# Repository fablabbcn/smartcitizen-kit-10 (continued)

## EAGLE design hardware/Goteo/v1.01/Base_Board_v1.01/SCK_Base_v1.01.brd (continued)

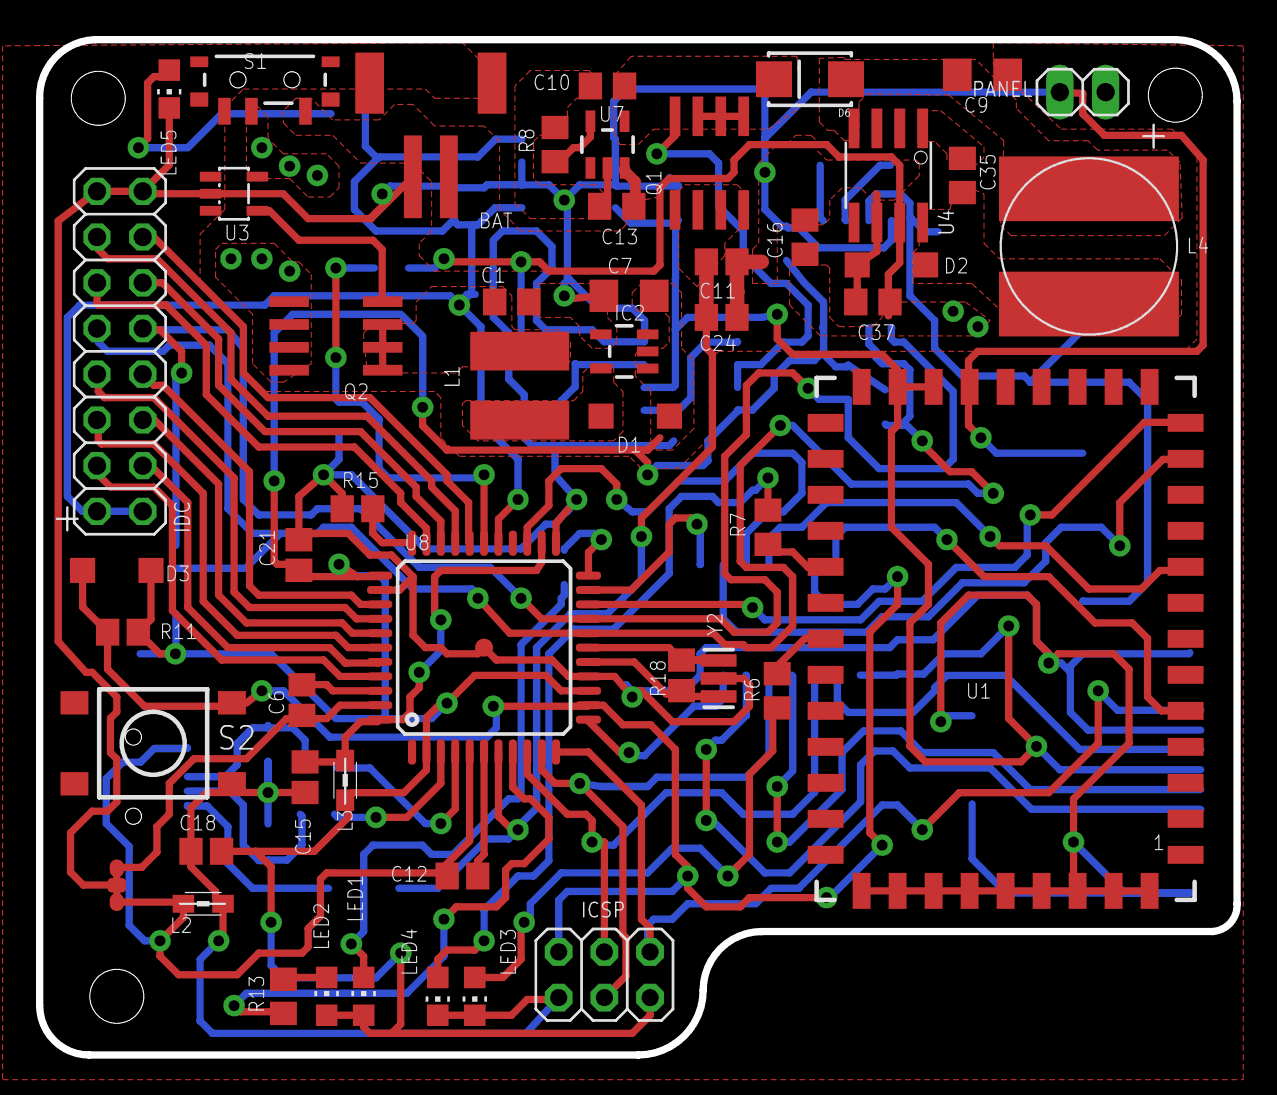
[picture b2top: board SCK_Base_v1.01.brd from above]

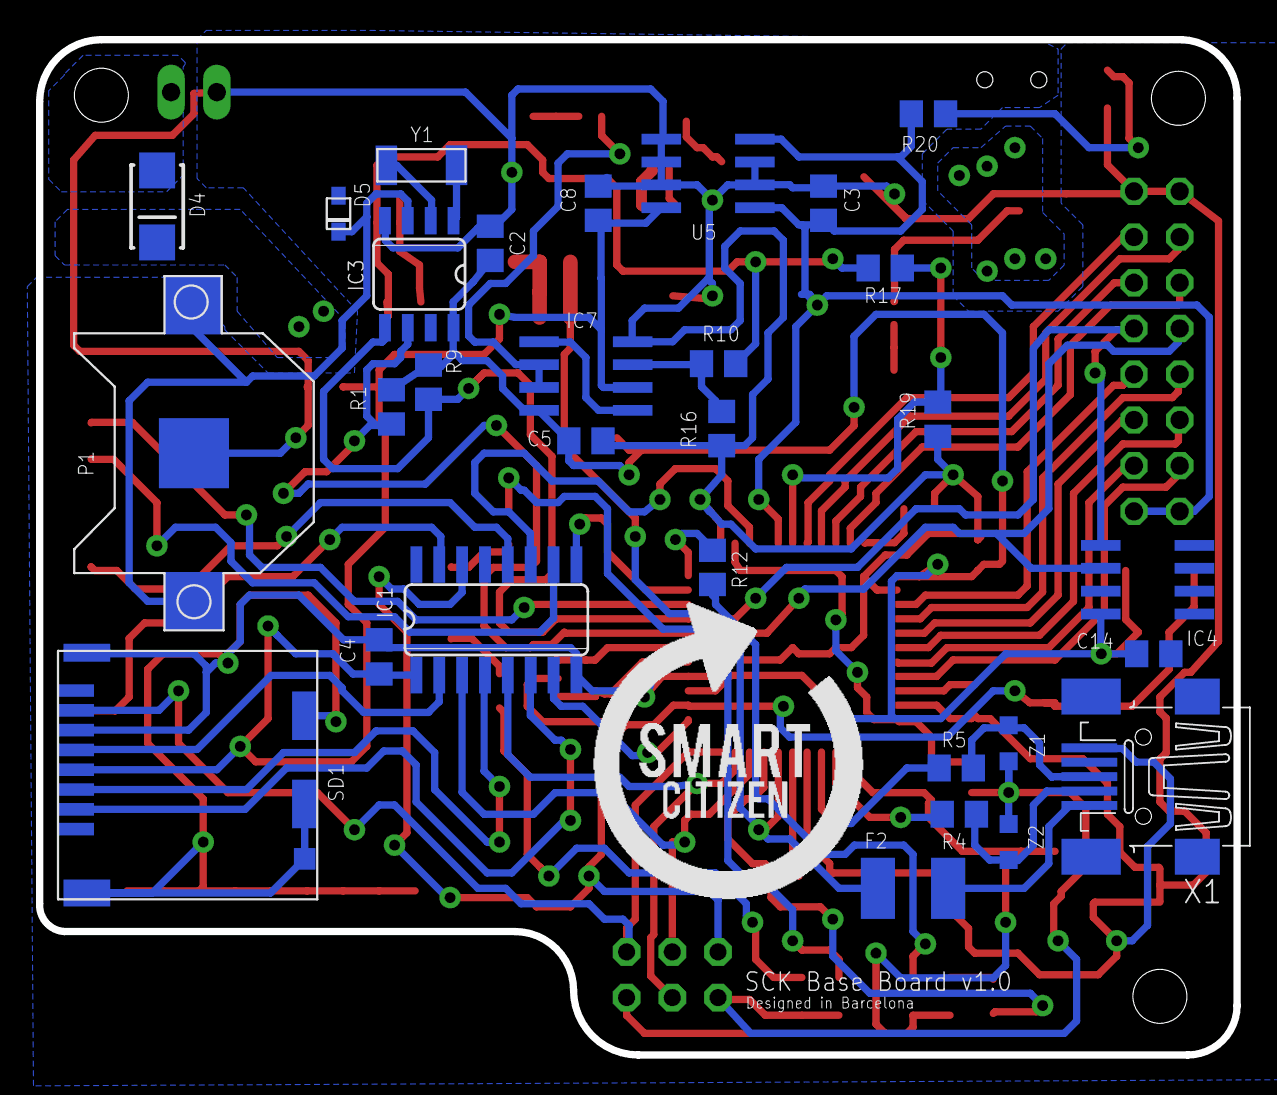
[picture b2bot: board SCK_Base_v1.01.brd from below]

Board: 2 copper layers, 66.5 x 56.4 mm, 81 parts (30 on the bottom side), 71 nets.

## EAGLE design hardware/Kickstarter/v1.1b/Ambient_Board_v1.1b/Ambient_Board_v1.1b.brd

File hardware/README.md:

Smart Citizen Kit
=================

###Smart Citizen Kit Ambient Sensor Board versions

| Smart Citizen Kit |           | SCK 1.0 (Goteo Board)       | SCK 1.1 (Kickstarter Board)       |
|:-----------|:---------:|:---------------------------:|:---------------------------:|
| **Data Board**        |           |                                                                                  |                                                                                     |
| **MCU**               |           | ATMEGA32U4                                                                       | ATMEGA32U4                                                                          |
| **Clock**             |           | 16Mhz                                                                            | 8Mhz                                                                                |
| **WiFi**             |           | Microchip RN-131 802.11 b/g                                                                            | Microchip RN-131 802.11 b/g                                                                                |
| **Firmware**         |           | https://github.com/fablabbcn/Smart-Citizen-Kit                                   | https://github.com/fablabbcn/Smart-Citizen-Kit                                      |
| **Design files**      |           | https://github.com/fablabbcn/Smart-Citizen-Kit/tree/master/hardware/Goteo/v1.01  | https://github.com/fablabbcn/Smart-Citizen-Kit/tree/master/hardware/Kickstarter     |
| **Ambient Board**     |           |                                                                                  |                                                                                     |
| **Light**             | *Part*      | PVD-P8001                                                                        | BH1730FVC                                                                           |
|                   | *Type*      | LDR Analog Light Sensor                                                          | Digital Ambient Light Sensor                                                        |
|                   | *Units*     | %                                                                                | Lux                                                                                 |
|                   | *Datasheet* | https://github.com/fablabbcn/Smart-Citizen-Kit/wiki/Datasheets/PDV-P8001.pdf     | https://github.com/fablabbcn/Smart-Citizen-Kit/wiki/Datasheets/BH-1730FCV.pdf       |
|                   | Firmware  | `SCKAmbient::getLight();`                                                           | `SCKAmbient::getLight():`                                                              |
| **Temp**              | *Part*      | DHT22                                                                            | HPP828E031 (SHT21)                                                                  |
|                   | *Type*      | Digital Temperature and Relative Humidity Sensor                                 | Digital Temperature and Relative Humidity Sensor                                    |
|                   | *Units*     | ºC                                                                               | ºC                                                                                  |
|                   | *Datasheet* | https://github.com/fablabbcn/Smart-Citizen-Kit/wiki/Datasheets/DHT22.pdf         | https://github.com/fablabbcn/Smart-Citizen-Kit/wiki/Datasheets/HTU-21D.pdf          |
|                   | Firmware  | `SCKAmbient::getDHT22();` `SCKAmbient::getHumidity();`                               | `SCKAmbient::getSHT21();` `SCKAmbient::getTemperature();`                               |
| **Humidity**          | *Part*      | DHT22                                                                            | HPP828E031 (SHT21)                                                                  |
|                   | *Type*      | Digital Temperature and Relative Humidity Sensor                                 | Digital Temperature and Relative Humidity Sensor                                    |
|                   | *Units*     | % Rel                                                                            | % Rel                                                                               |
|                   | *Datasheet* | https://github.com/fablabbcn/Smart-Citizen-Kit/wiki/Datasheets/DHT22.pdf         | https://github.com/fablabbcn/Smart-Citizen-Kit/wiki/Datasheets/HTU-21D.pdf          |
|                   | Firmware  | `SCKAmbient::getDHT22();` `SCKAmbient::getHumidity();`                               | `SCKAmbient::getSHT21();` `SCKAmbient::getHumidity();`                                  |
| **Noise**             | *Part*      | POM-3044P-R                                                                      | POM-3044P-R                                                                         |
|                   | *Type*      | Electret microphone with envelop follower sound pressure sensor                  | Electret microphone with envelop follower sound pressure sensor                     |
|                   | *Units*     | dB                                                                               | dB                                                                                  |
|                   | *Datasheet* | https://github.com/fablabbcn/Smart-Citizen-Kit/wiki/Datasheets/POM-3044P-R.pdf   | https://github.com/fablabbcn/Smart-Citizen-Kit/wiki/Datasheets/POM-3044P-R.pdf      |
|                   | *Firmware*  | `SCKAmbient::getNoise();`                                                          | `SCKAmbient::getNoise();`                                                             |
| **CO**                | *Part*      | MICS-5525                                                                        | MiCS-4514                                                                           |
|                   | *Type*      | MOS CO gas sensor                                                                | MOS CO and NO2 gas sensor                                                           |
|                   | *Units*     | kOhm (ppm)                                                                       | kOhm (ppm)                                                                          |
|                   | *Datasheet* | https://github.com/fablabbcn/Smart-Citizen-Kit/wiki/Datasheets/MICS-5525_CO.pdf  | https://github.com/fablabbcn/Smart-Citizen-Kit/wiki/Datasheets/MiCS-4514_CO_NO2.pdf |
|                   | *Firmware*  | `SCKAmbient::getMICS();`                                                           | `SCKAmbient::getMICS();`                                                              |
| **NO2**               | *Part*      | MICS-2710                                                                        | MiCS-4514                                                                           |
|                   | *Type*      | MOS NO2 gas sensor                                                               | MOS CO and NO2 gas sensor                                                           |
|                   | *Units*     | kOhm (ppm)                                                                       | kOhm (ppm)                                                                          |
|                   | *Datasheet* | https://github.com/fablabbcn/Smart-Citizen-Kit/wiki/Datasheets/MICS-2710_NO2.pdf | https://github.com/fablabbcn/Smart-Citizen-Kit/wiki/Datasheets/MiCS-4514_CO_NO2.pdf |
|                   | *Firmware*  | `SCKAmbient::getMICS();`                                                           | `SCKAmbient::getMICS();`                                                              |

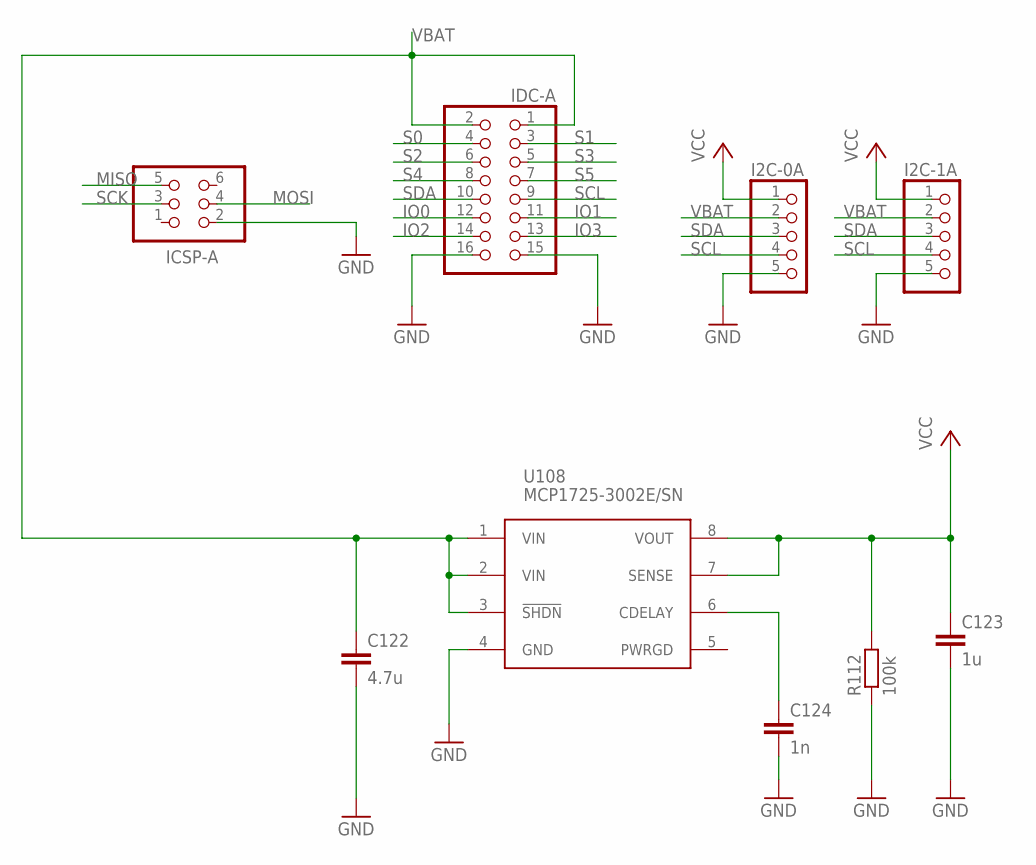
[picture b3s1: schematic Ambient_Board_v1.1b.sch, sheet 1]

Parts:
C122: 4.7u; C0805
C123: 1u; C0805
C124: 1n; C0603K
I2C-0A, I2C-1A: PINHD-1X5; 1X05
ICSP-A: ICSP-A; 2X03
IDC-A: PINHD-2X8; 2X08
R112: 100k; R0603
U108: MCP1725-3002E/SN; SOIC8

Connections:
GND: C122.2, C123.2, C124.2, I2C-0A.5, I2C-1A.5, ICSP-A.2, IDC-A.15, IDC-A.16, R112.1, U108.4 (GND); also elsewhere on the board
IO0: IDC-A.12; also elsewhere on the board
IO1: IDC-A.11; also elsewhere on the board
IO2: IDC-A.14; also elsewhere on the board
IO3: IDC-A.13; also elsewhere on the board
MISO: ICSP-A.5
MOSI: ICSP-A.4
unnamed: C124.1, U108.6 (CDELAY)
S0: IDC-A.4; also elsewhere on the board
S1: IDC-A.3; also elsewhere on the board
S2: IDC-A.6; also elsewhere on the board
S3: IDC-A.5; also elsewhere on the board
S4: IDC-A.8; also elsewhere on the board
S5: IDC-A.7
SCK: ICSP-A.3
SCL: I2C-0A.4, I2C-1A.4, IDC-A.9; also elsewhere on the board
SDA: I2C-0A.3, I2C-1A.3, IDC-A.10; also elsewhere on the board
VBAT: C122.1, I2C-0A.2, I2C-1A.2, IDC-A.1, IDC-A.2, U108.1 (VIN), U108.2 (VIN), U108.3 (!SHDN); also elsewhere on the board
VCC: C123.1, I2C-0A.1, I2C-1A.1, R112.2, U108.7 (SENSE), U108.8 (VOUT); also elsewhere on the board

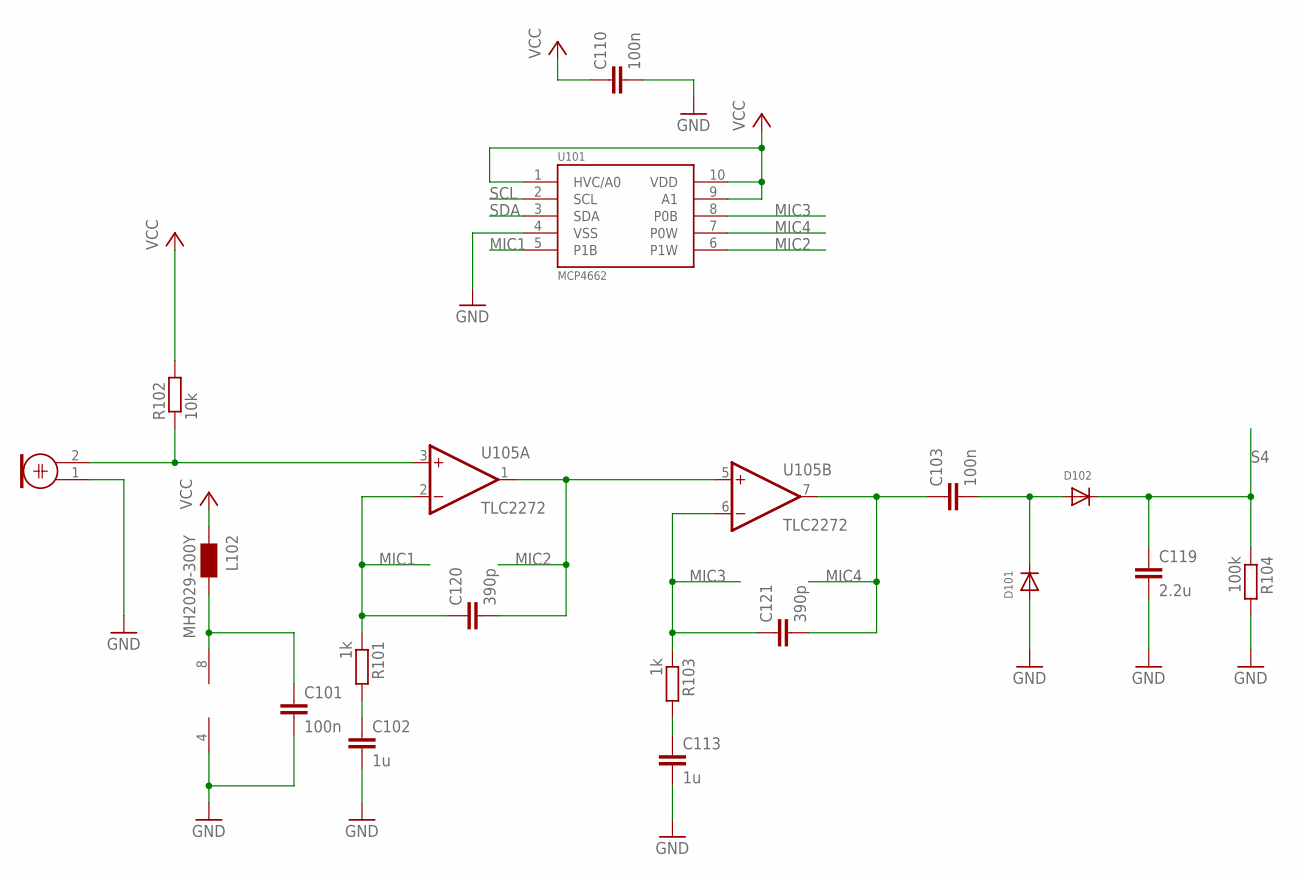
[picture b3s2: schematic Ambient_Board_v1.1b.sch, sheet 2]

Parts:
C101, C103, C110: 100n; C0603
C102, C113: 1u; C0805
C119: 2.2u; C0805
C120, C121: 390p; C0603
D101, D102: DIODESOD-323F; SOD-323F
L102: MH2029-300Y; 0805
M101: POM-3044P-R; WM-63PR
R101, R103: 1k; R0603
R102: 10k; R0603
R104: 100k; R0603
U101: MCP4662; MSOP10
U105: TLC2272; SO08

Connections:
GND: C101.2, C102.2, C110.2, C113.2, C119.2, D101.A, M101.1, R104.2, U101.4 (VSS), U105.4 (V-); also elsewhere on the board
MIC1: C120.1, R101.1, U101.5 (P1B), U105.2 (-IN)
MIC2: C120.2, U101.6 (P1W), U105.1 (OUT), U105.5 (+IN)
MIC3: C121.1, R103.1, U101.8 (P0B), U105.6 (-IN)
MIC4: C103.1, C121.2, U101.7 (P0W), U105.7 (OUT)
unnamed: M101.2, R102.1, U105.3 (+IN)
unnamed: C102.1, R101.2
unnamed: C103.2, D101.C, D102.A
unnamed: C101.1, L102.2, U105.8 (V+)
unnamed: C113.1, R103.2
S4: C119.1, D102.C, R104.1; also elsewhere on the board
SCL: U101.2 (SCL); also elsewhere on the board
SDA: U101.3 (SDA); also elsewhere on the board
VCC: C110.1, L102.1, R102.2, U101.1 (HVC/A0), U101.9 (A1), U101.10 (VDD); also elsewhere on the board

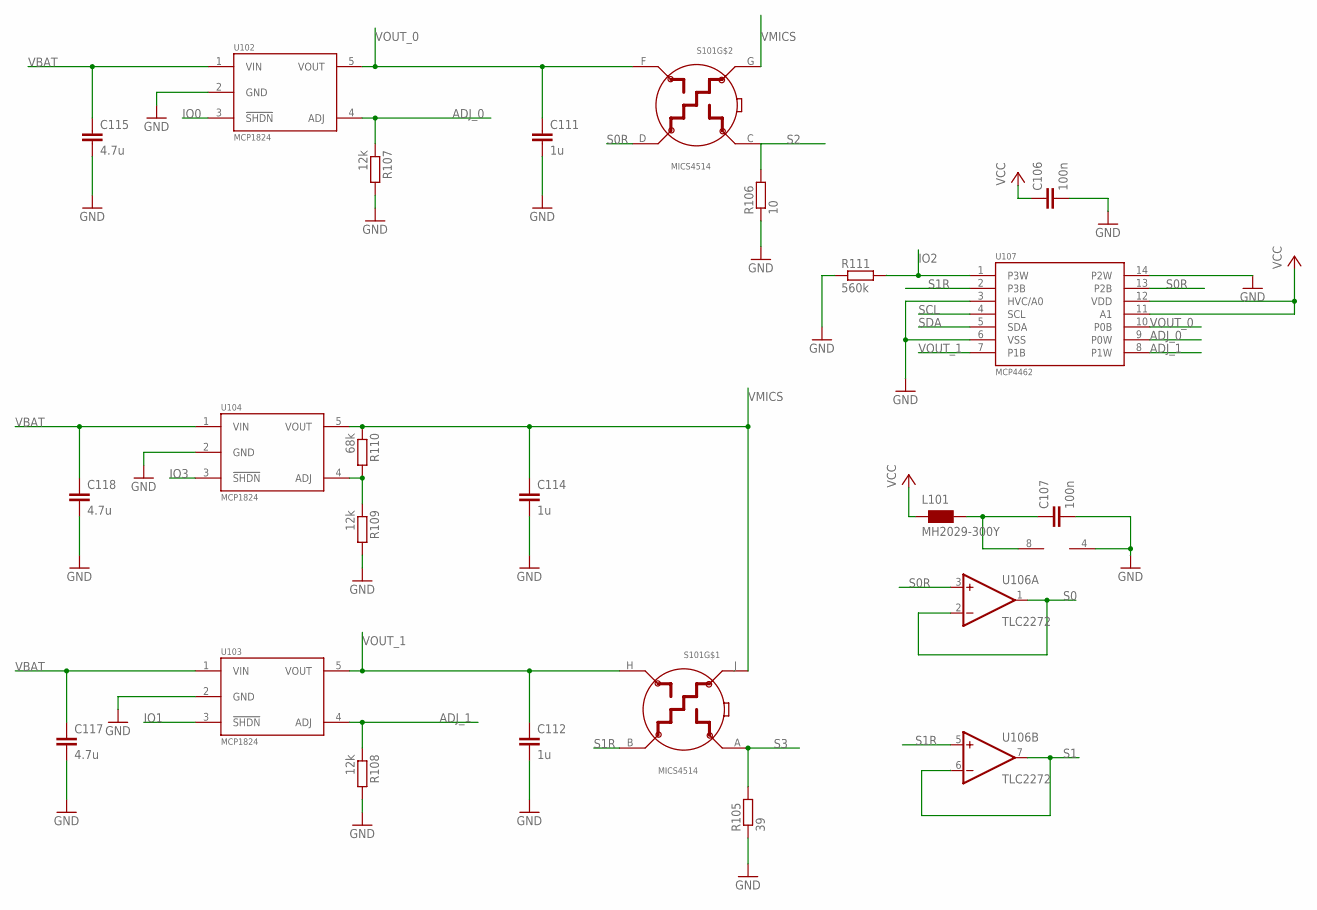
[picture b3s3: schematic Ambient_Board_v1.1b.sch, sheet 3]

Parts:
C106, C107: 100n; C0603
C111, C112, C114: 1u; C0805
C115, C117, C118: 4.7u; C0805
L101: MH2029-300Y; 0805
R105: 39; R0603
R106: 10; R0603
R107, R108, R109: 12k; R0603
R110: 68k; R0603
R111: 560k; R0603
S101: MICS4514; MICS_SMD
U102, U103, U104: MCP1824; SOT23-5L
U106: TLC2272; SO08
U107: MCP4462; TSSOP14

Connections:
ADJ_0: R107.1, U102.4 (ADJ), U107.9 (P0W)
ADJ_1: R108.1, U103.4 (ADJ), U107.8 (P1W)
GND: C106.2, C107.2, C111.2, C112.2, C114.2, C115.2, C117.2, C118.2, R105.1, R106.1, R107.2, R108.2, R109.2, R111.1, U102.2 (GND), U103.2 (GND), U104.2 (GND), U106.4 (V-), U107.3 (HVC/A0), U107.6 (VSS), U107.14 (P2W); also elsewhere on the board
IO0: U102.3 (!SHDN); also elsewhere on the board
IO1: U103.3 (!SHDN); also elsewhere on the board
IO2: R111.2, U107.1 (P3W); also elsewhere on the board
IO3: U104.3 (!SHDN); also elsewhere on the board
unnamed: C107.1, L101.2, U106.8 (V+)
unnamed: R109.1, R110.2, U104.4 (ADJ)
S0: U106.1 (OUT), U106.2 (-IN); also elsewhere on the board
S0R: S101.D (4), U106.3 (+IN), U107.13 (P2B)
S1: U106.6 (-IN), U106.7 (OUT); also elsewhere on the board
S1R: S101.B (4), U106.5 (+IN), U107.2 (P3B)
S2: R106.2, S101.C (1); also elsewhere on the board
S3: R105.2, S101.A (1); also elsewhere on the board
SCL: U107.4 (SCL); also elsewhere on the board
SDA: U107.5 (SDA); also elsewhere on the board
VBAT: C115.1, C117.1, C118.1, U102.1 (VIN), U103.1 (VIN), U104.1 (VIN); also elsewhere on the board
VCC: C106.1, L101.1, U107.11 (A1), U107.12 (VDD); also elsewhere on the board
VMICS: C114.1, R110.1, S101.G (2), S101.J (2), U104.5 (VOUT)
VOUT_0: C111.1, S101.F (3), U102.5 (VOUT), U107.10 (P0B)
VOUT_1: C112.1, S101.H (3), U103.5 (VOUT), U107.7 (P1B)

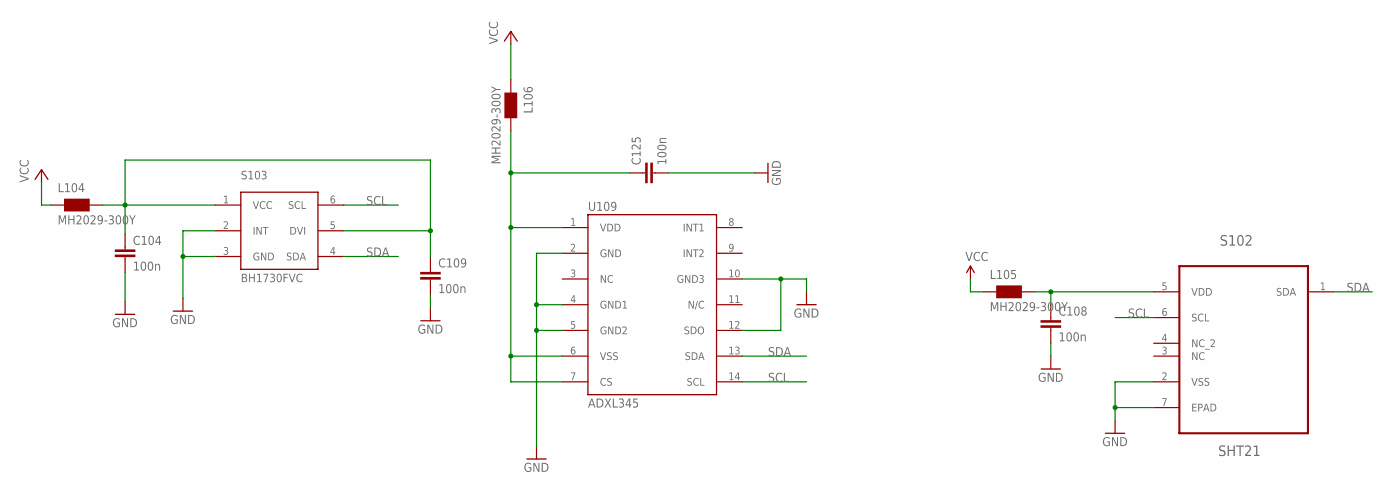
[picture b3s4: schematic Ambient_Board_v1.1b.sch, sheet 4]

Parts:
C104, C108, C109, C125: 100n; C0603
L104, L105, L106: MH2029-300Y; 0805
S102: SHT21; DFN300X300X110-7N
S103: BH1730FVC; WSOF6
U109: ADXL345; LGA14

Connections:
GND: C104.2, C108.2, C109.2, C125.2, S102.2 (VSS), S102.7 (EPAD), S103.2 (INT), S103.3 (GND), U109.2 (GND), U109.4 (GND1), U109.5 (GND2), U109.10 (GND3), U109.12 (SDO); also elsewhere on the board
unnamed: C125.1, L106.2, U109.1 (VDD), U109.6 (VSS), U109.7 (CS)
unnamed: C108.1, L105.2, S102.5 (VDD)
unnamed: C104.1, C109.1, L104.2, S103.1 (VCC), S103.5 (DVI)
SCL: S102.6 (SCL), S103.6 (SCL), U109.14 (SCL); also elsewhere on the board
SDA: S102.1 (SDA), S103.4 (SDA), U109.13 (SDA); also elsewhere on the board
VCC: L104.1, L105.1, L106.1; also elsewhere on the board

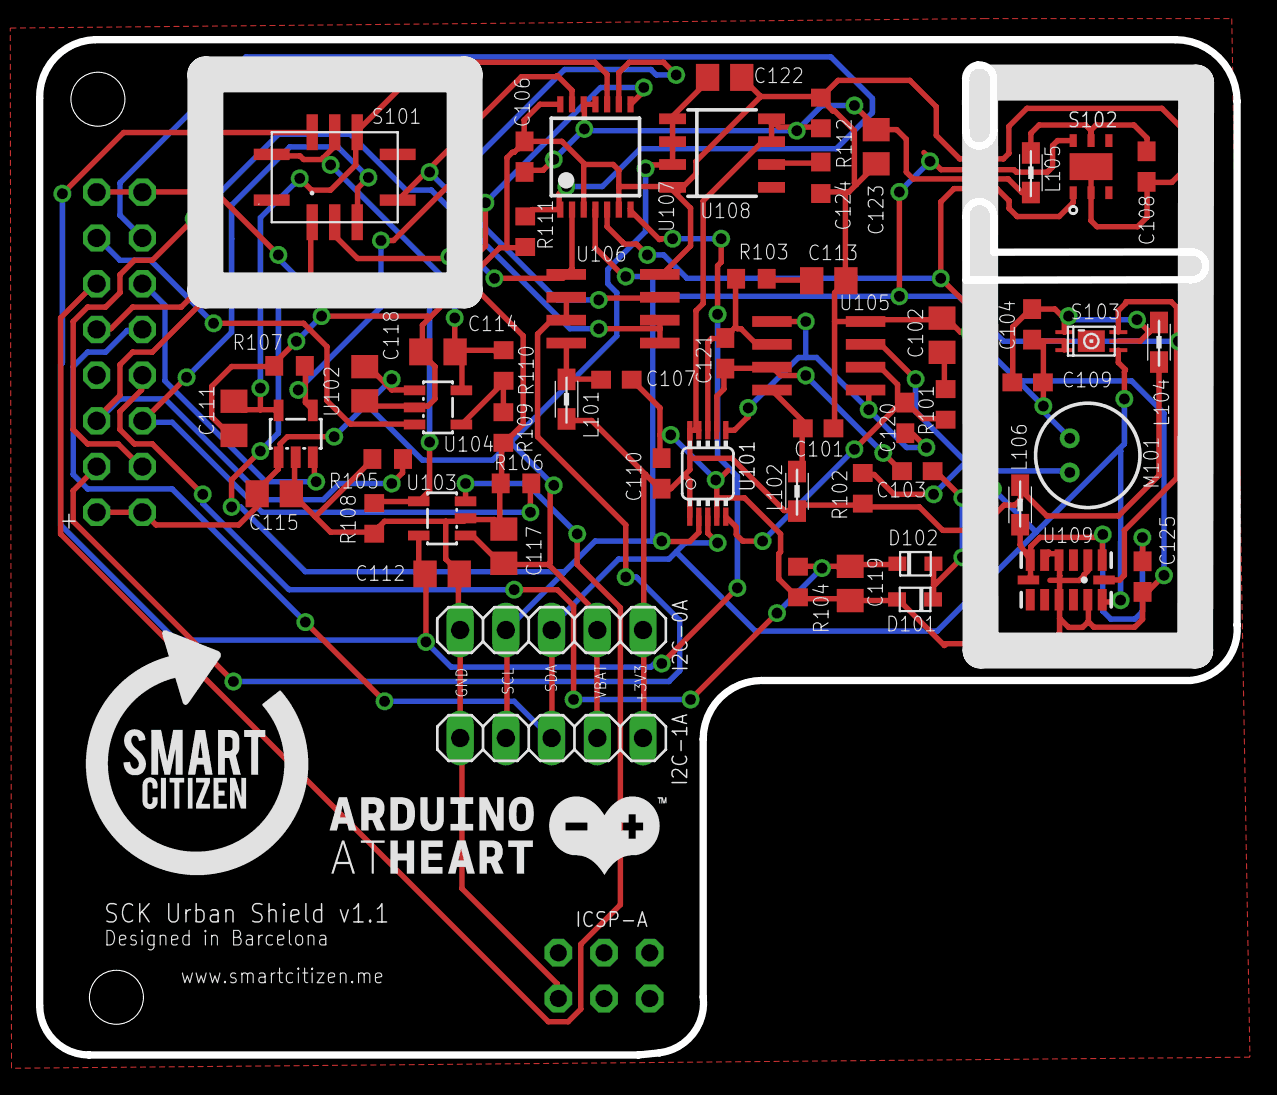
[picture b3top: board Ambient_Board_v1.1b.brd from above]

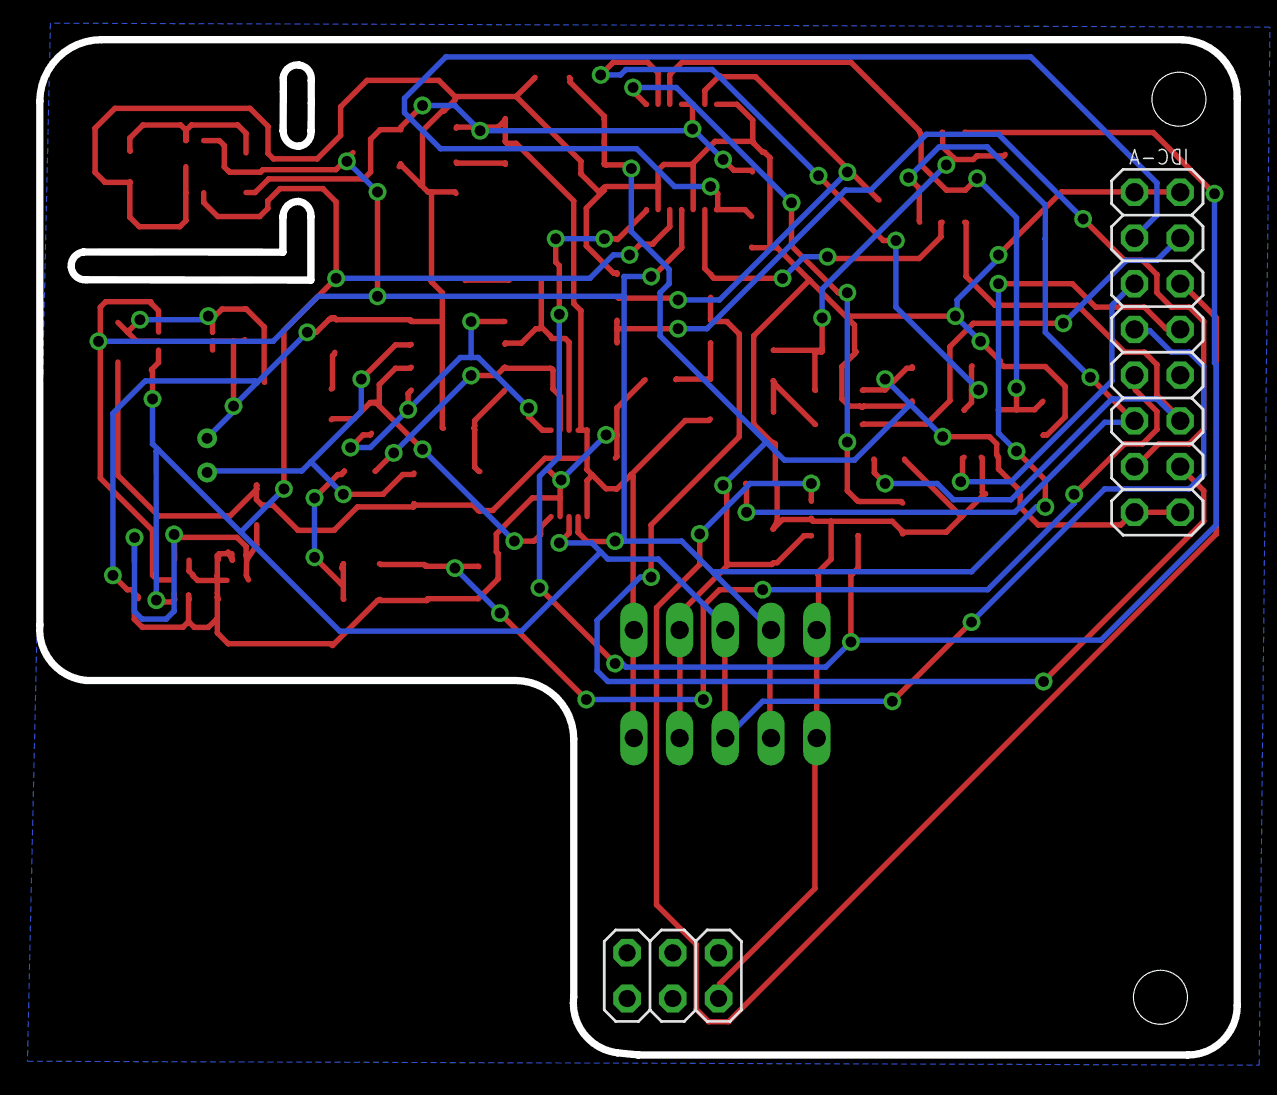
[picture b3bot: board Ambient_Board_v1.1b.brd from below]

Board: 2 copper layers, 66.5 x 56.4 mm, 59 parts (2 on the bottom side), 36 nets.

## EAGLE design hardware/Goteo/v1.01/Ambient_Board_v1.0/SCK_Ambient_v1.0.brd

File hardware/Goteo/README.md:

Smart-Citizen-Kit
=================

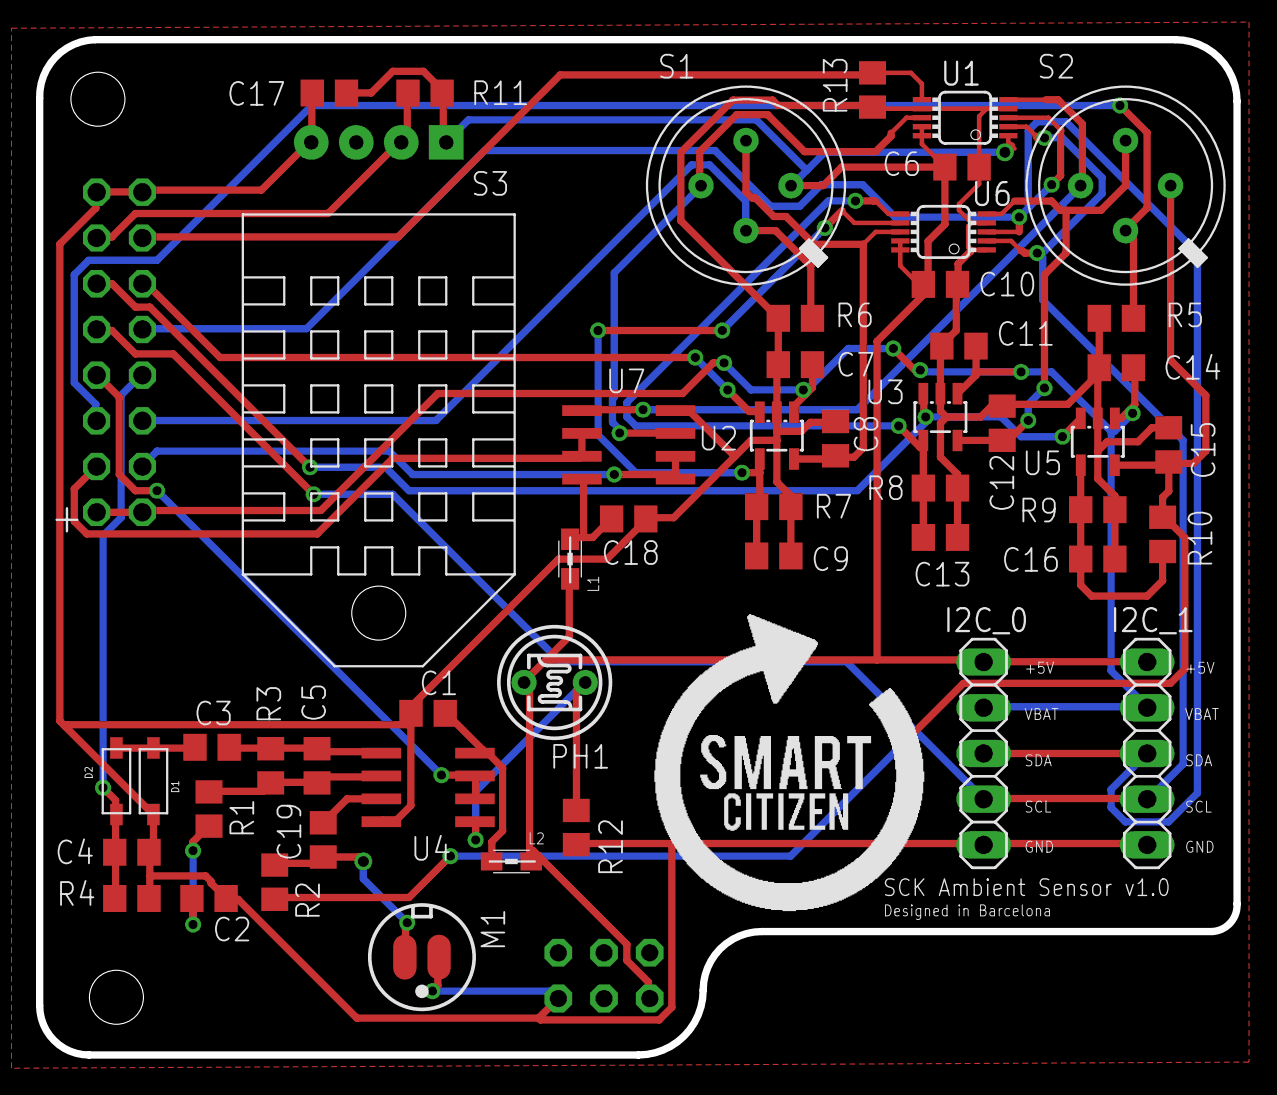
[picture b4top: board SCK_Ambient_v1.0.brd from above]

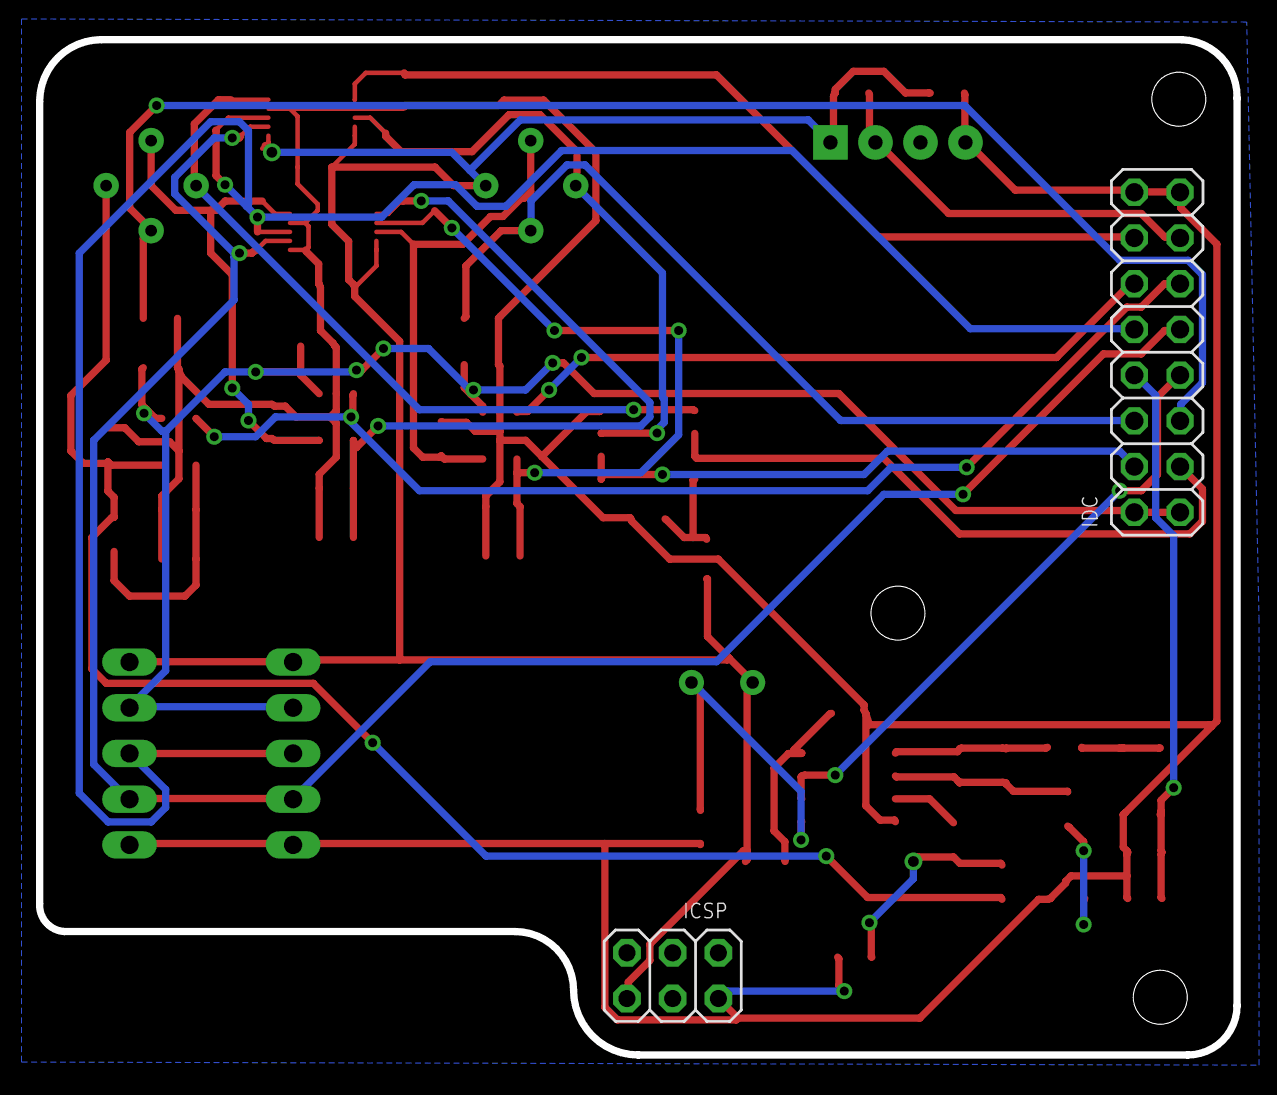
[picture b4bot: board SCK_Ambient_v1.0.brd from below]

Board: 2 copper layers, 66.5 x 56.4 mm, 52 parts (2 on the bottom side), 32 nets.

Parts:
C1, C3, C6, C10, C17, C18: 100n; C0805
C2, C4, C19: 2.2u; C0805
C5: 10p; C0805
C7, C8, C11, C12, C14, C15: 10u; C0805
C9, C13, C16: 100p; C0805
D1, D2: SOD-123
I2C_0, I2C_1: 1X05
ICSP: ICSP; 2X03
IDC: 2X08
L1, L2: MH2029-300Y; 0805
M1: ELECTRET_MICROPHON-WM-61A; WM-61A
PH1: A1050_09; T0-46-A10XX
R1: 4K7; R0805
R2: 10K; R0805
R3, R13: 560k; R0805
R4: 100K; R0805
R5, R6: 10; R0805
R7, R8: 82k; R0805
R9: 180K; R0805
R10: 200K; R0805
R11: 1K; R0805
R12: 2K2; R0805
S1: MICS-5525; E2V
S2: MICS-2710; E2V
S3: RHT22
U1, U6: MCP4662; MSOP10
U2, U3, U5: TC1071; SOT23-5L
U4, U7: TL082D; SO08

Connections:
+5V: C6.1, C10.1, C17.1, I2C_0.1, I2C_1.1, ICSP.6, L1.1, L2.1, PH1.1, R11.1, S1.2, S3.1, U1.1, U1.9, U1.10, U6.9, U6.10
ADJ_0: C9.1, R7.1, U2.4, U6.7
ADJ_1: C13.1, R8.1, U3.4, U6.6
ADJ_2: C16.1, R9.1, R10.2, U5.4
GND: C1.2, C2.2, C4.2, C6.2, C7.2, C8.2, C9.2, C10.2, C11.2, C12.2, C13.2, C14.2, C15.2, C16.2, C17.2, C18.2, D1.A, I2C_0.5, I2C_1.5, ICSP.2, IDC.15, IDC.16, M1.1, R4.2, R5.1, R6.1, R7.2, R8.2, R9.2, R12.2, R13.1, S3.4, U1.4, U1.7, U2.2, U3.2, U4.4, U5.2, U6.1, U6.4, U7.4
IO0: IDC.12, U2.3
IO1: IDC.11, U3.3, U5.3
IO2: IDC.14, R13.2, U1.6
IO3: IDC.13, R11.2, S3.2
unnamed: C19.1, M1.2, R2.1
unnamed: C2.1, R1.2
unnamed: C3.2, D1.C, D2.A
unnamed: C5.1, R1.1, R3.2, U4.2
unnamed: C3.1, C5.2, R3.1, U4.1
unnamed: C1.1, L2.2, U4.8
unnamed: C18.1, L1.2, U7.8
unnamed: PH1.2, R12.1, U4.5
unnamed: C19.2, U4.3
S0: IDC.4, U7.1, U7.2
S0R: S1.4, U1.8, U7.3
S1: IDC.3, U7.6, U7.7
S1R: S2.4, U1.5, U7.5
S2: IDC.6, R6.2, S1.1
S3: IDC.5, R5.2, S2.1
S4: C4.1, D2.C, IDC.8, R4.1
S5: IDC.7, U4.6, U4.7
SCL: I2C_0.4, I2C_1.4, IDC.9, U1.2, U6.2
SDA: I2C_0.3, I2C_1.3, IDC.10, U1.3, U6.3
VBAT1: C7.1, C11.1, C14.1, I2C_0.2, I2C_1.2, IDC.1, IDC.2, U2.1, U3.1, U5.1
VOUT_0: C8.1, S1.3, U2.5, U6.8
VOUT_1: C12.1, S2.3, U3.5, U6.5
VOUT_2: C15.1, R2.2, R10.1, S2.2, U5.5

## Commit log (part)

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2013-02-09 first demo code
2013-02-10 SCK BETA V0.3
    Pushing the Sck_test_beta_v0_3 firmware for the SmartCitizen KIT
2013-02-11 Fixed some bugs in the startup process. Sometimes the wifi module crashes. Necessary to update the firmware to 2.38.3
2013-02-11 Added sketch to control wifly module using Arduino terminal. Recommended update firmware after connecting to wifly network. Command: "ftp upload" + enter
2013-02-11 Revert "no message"
    This reverts commit b9999eb610b8e5de27009ff5f1576d843702d1a4.
2013-02-11 readme file
2013-02-12 Added sketch to control wifly module using Arduino terminal. Recommended update firmware after connecting to wifly network.
2013-02-14 Info to upload firmware and restart wifly module to factory setup
2013-04-24 New version compatible with COSM. Change the SSID and password in configDefault file, then change your feed and APIKEY.
2013-04-24 Sketch for updating WIFly firmware. Put your SSID and password in the main program Sck_ftp_update.ino
2013-04-24 minor changes
2013-04-26 Solved problem with smart citizen kit usb configuration using Smart Citizen platform.
2013-06-01 solved problem when wifi is disconnected for a long time!
2013-07-24 Eagles files of Goteo.org campaign http://www.goteo.org/project/smart-citizen-sensores-ciudadanos
    Smart Citizen Kit BETA version
    - Base Board v1.0
    - Ambient Sensor Board v1.0
2013-07-24 Base Board v1.01 Some improvements:
    - Wifly 3V3 RIN connected to GND
    - Adding new diode for the battery of RTC
2013-08-11 Some problems with eagle original files. Uploaded sources in zip format.
2013-10-01 Nueva version
2013-10-01 Nueva versión
    Se a eliminado gran parte de la libreria SmartCitizen y simplificado
    alguna funciones.
    Añadida compatibilidad a la version 1.1 del SCK Board y Ambient
2013-10-01 Fallo corregido provisionalmente, tiene un desbordamiento de memoria y solo acepta preconfigurar dos redes de memoria.
2013-10-01 Correcciones de cuelgues
2013-10-08 Adquirida compensacion de temperatura by armadillu
2013-10-08 Adquirida mencion al creador de la libreia I2C utilizada
2013-10-19 Correcciones en los sensores de gas
2013-10-19 Correccion de valores negativos de temperatura que provocaba un error al postear
2013-10-20 Adquirida ecuación de conversión a ppm de los sensores de gas
2013-10-27 Cambios introducidos por aposada
2013-10-27 actualizado
2013-10-27 Correcciones en la SD
2013-10-28 Corregido fallo en el primer post del sensor de luz
2013-10-28 Añadido ajuste de reloj de la RTC cada vez que conecta al servidor.
2013-11-04 Actualizada la RTC al chip DS1339
2013-12-09 Limpieza de codigo y se puede seleccionar entre modo RAW y "normal"
2013-12-09 Nueva version del firmware
2013-12-09 Revert "Nueva version del firmware"
    This reverts commit 14413ed2e1d3c47728bc4939659fe5b9d16b2a45.
2013-12-09 Revert "Revert "Nueva version del firmware""
    This reverts commit 48708747a4e2fb564135b2baacb12a41b3a75624.
2013-12-09 Revert "Revert "Revert "Nueva version del firmware"""
    This reverts commit 76695489e06d827ac74d6207b5496909c3cbbf43.
2013-12-09 Correcciones en la RTC
2013-12-11 Activado modo "RAW" y adquirida lista de comandos.
2013-12-11 Añadido nuevo comando
2013-12-13 Correccion medicion de la bateria
2013-12-14 Adquirido nuevo comando para setear el numero de actualizaciones a la vez
2013-12-15 Cambios en las ecuaciones de audio
2013-12-16 Adquirido numero de subversion
2013-12-18 Adquirida version de placa.
2014-01-08 Adquirido modo RAW para los SmartCitizenKit v1.0
2014-01-09 Deshabilitado el modo AP automatico cuando no detecta redes disponibles.
    Ahora solo entra en modo AP cuando se arranca la placa por primera vez.
2014-01-09 Correcciones en modo AP
2014-01-09 Adquirido comando #data para visualizar los datos de la EEPROM
2014-01-09 Adquirido nuevo comando en la lista de comandos
2014-01-10 ajustes del modo AP
2014-01-14 manual cleaning
2014-01-14 clean
2014-01-14 v0.3.0
2014-01-14 v0.6.2
2014-01-14 v0.8.4
2014-01-14 v0.8.5
2014-01-15 updated hardware and readme info
2014-01-16 repo restructure
2014-01-16 links after mig
2014-01-16 Correccion en el checkeo de la EEPROM
2014-01-16 Correccion en la lectura de la EEPROM que puede producir cuelgue del kit
2014-01-16 Importante!! Corrección en la constante VCC, que produce que los valores leeidos en todos los SCK v1.1 sean erroneos!!
2014-01-17 Adquirido provisionalmente el acelerometro ADXL345
2014-01-25 Added full firm and mac commands to sck custom terminal
    Commands added to support the new config under the custom "###"
    terminal mode
2014-02-03 serial bridge WiFly to USB limited CMD Mode
    WiFly Serial Bridge limited to WiFly commands mode to prevent undesired
    debug info when in SCK command mode
2014-02-03 Code Formatting
2014-02-16 Update sck-commands.md
    Fix some spelling an grammar issues.
2014-03-09 Testing wifly acquired
2014-03-09 Wifly_Rescue.ino acquired
2014-03-12 Wifly_Update.ino acquired
2014-03-14 0.8.6 Ready for release
    - Added: WiFly Baudrate autodetect and repair
    - Added: WiFly Auto firmware update
2014-03-18 New utilities and compensation of analog reference voltage
    Utilities:
    Wifly_Update.ino
    Wifly_Rescue.ino
2014-03-18 Now also compiles in Arduino IDE 1.5.6
2014-03-20 SD version adquired
2014-03-21 Improved USB communication, and SD card only version
2014-03-21 Improved USB communication
2014-03-21 Autoupdate correction
2014-03-22 Add ftp server
2014-03-22 Fixed bug in terminal mode
2014-03-23 New version of wifly_terminal
2014-03-23 Connection changes
2014-04-09 New SCK_check
2014-04-10 update sck_check
2014-04-10 update2 sck_check
2014-04-10 update 2 sck_check
2014-04-11 0.8.6 public release
2014-04-15 Translated to English
2014-04-17 release 0.8.6
2014-04-17 release
2014-04-17 release 0.8.6 readme fixes
2014-04-17 Acquired new beta version 0.9
2014-04-17 Keywords deleted
2014-04-18 Changes in SCK_check utilitie.
2014-04-22 DataRaw FirmwareVersion preprocessor bug
2014-04-22 #endif wrongly declared
2014-04-22 remove changes merge file
2014-04-22 debugg disabled
2014-04-22 Translated into English
2014-04-23 Directory reorganized
2014-05-02 Adquired first version of economic mode
    - Now also acquires although the number of networks in AP mode
2014-05-03 Correction in economic mode
2014-07-21 Release 0.9.0
2014-08-09 - Added GNU GPL license in all files. - Implemented 'set apikey' command. - Added 'base_.' prefix in in heat(.) function.
2014-08-09 Strictly greater comparison 'val > 1.0f - GHETTO_VAL'.
2014-08-09 Comment moved out of the define
2014-08-09 Comments moved out of the define
2014-08-09 Code constructions improvements
2014-08-10 Created functions to prevent code redundancy
2014-08-11 Updated the SCK serial commands reference
2014-08-11 Created singleton unique static objects for ambient, base, and server
2014-08-11 Created functions readByte and writeByte to prevent code redundancy
2014-08-15 Use i2c_write_many
2014-09-23 Added REAME for SD data conversion
2014-10-12 fixed bug in autoupdate
2014-10-12 Revert "fixed bug in autoupdate"
    This reverts commit 623a83500125bb66108c16e2cb8840cebe86df68.
2014-10-12 Revert "Revert "fixed bug in autoupdate""
    This reverts commit a4de0910d0964d00a6f5348200d6ab2b041a2435.
2014-11-01 Added .gitignore
2014-11-02 Added doxygen documentation comments
2014-11-02 Bug in addData, due to bad merge
2014-11-02 Test mode only for F_CPU == 8000000 so far
2014-11-19 Missing base_. when begun mode is on
    Small change adding base._average in line 329
2014-11-27 Removed unused readCharge() function
2014-11-27 Added MCP3 constant
2014-12-01 Updating the EAGLE doc
2015-02-18 sdfat library well implemented and csv file header addded
2015-02-19 csv header format improved
2015-02-19 data raw conversion implemented when you set DataRaw to true in Constants.h file
2015-02-25 SD documentation updated
2015-03-04 Adding hardware core boards support
2015-03-06 web app demo beta
2015-03-16 .gitignore
2015-03-19 Port to SAMD21 WIP
2015-04-09 Detailed hardware documentation
2015-04-09 Table design
2015-04-09 Doc details
2015-05-13 pdf hardware doc
2015-06-04 SD docs
2015-06-07 Custom backend example
2015-06-23 Fix HTTP message formatting to be RFC2616 (section 5.1) compliant, and hence so they will pass through a transparent Squid proxy
2015-07-03 version updated
2015-07-16 Fix overflow on serial, print txDebug
2015-07-31 Revert 535b851..45a6503
    This rolls back to commit 535b851528311b3f5b8fb4cbbe1c756d15124a54.
2015-08-13 Disable LED's command
2016-03-15 Changes in the RTC and upgrade module wifly
2016-03-15 Revert "Disable LED's command"
    This reverts commit dd180889e35dd74b51b57e7c625ea07c6de8cff8.
2016-03-15 New command "clear memory"
2016-03-16 Memory limit protection activated
2016-04-10 Added eeprom memory sanity check on boot.
    -Removed __TIME__ as the method for detecting first boot, since it's behavior is not the same in all systems.
    -Added function eepromCheck() that checks eeprom variable sanity and if necessary executes a clearmemory().
    -eepromCheck() also checks for hardcoded nets and overwrite them if necessary.
    -Updated "clear nets" command to only clear non harcoded networks (allowing use of the remaining slots for nets added by configurator).
2016-04-10 Fix wrong timestamp after connection error.
    When sending multiple posts after a connection error all the timestamps but the last one where the same.
    It wasn't getting RTC time before saving the post to memory.
2016-04-11 "Get all" command now reports the number of hardcoded netwoks.
2016-04-14 Don't send data if RTC hasn't been updated since boot
    -If RTC is not working don't capture and don't send data, make error visible to user (blue leds keep blinking permanently).
    -Added function RTCupdate() grouping commands.
    -version change to 0.9.3-A
    -Minor changes
2016-04-25 Minor bug fix
    - Don't print debug message if we are in command mode
2016-05-05 Added support for external temp sensor - DS18B20
2016-05-05 New script for testing and updating Smartcitizen Kits
2016-05-05 Minor content correction
2016-05-06 Added screenshot to readme
2016-05-06 MacOS port
2016-06-02 Fix for unnecessary clear memory
    The function MAC() now returns -1 when wifly don't give us a valid mac address.
    Keep asking wifly for mac address until we get a valid response, avoiding unnecessary clearMemory().
2016-06-06 Fix error that prevents certain commands to work
    Added second parameter when calling printNetworks from _get wlan_ commands
2016-06-09 New battery percent calculation
    Based on a lookup table now battery percent reporting is more accurate.
2016-06-16 Make changes to time update instant.
    Now when time update interval is changed via "set time update" changes take effect instanlty, you don't have to wait until next post loop.
2016-06-16 Minor fixes
2016-06-16 Improved Wifi management
    * Removed automatic entering in APmode if no network is configured yet.
    * Report error in wifi connection including ssid and pass used.
    * If no connection has been made since boot don't enter sleep mode, keep trying and make error visible with blue leds.
    * Try to make a post immediately after boot.
    * Now a reboot is not needed after changed networks via the configurator if no connection has been made since boot.
2016-06-17 Minor added feedback on connection error
2016-06-17 Fix issue #38 "Update times are not regular"
2016-06-21 Support again coin cell battery RTC in case of temporary network error.
2016-07-21 Proper version number
2016-07-21 Readme.md version change
2016-07-22 Minor feedback improvements
2016-07-22 Enclosure initial readme
2016-07-25 Added old case and reorganize.
2016-07-25 more reorganization.
2016-10-25 Create Smart Citizen SCK Mock-Up
    Smart Citizen SCK Mock-Up that can be 3D printed for testing and fitting so the real hardware won't need to be used.
2016-10-25 Dummy Top Plate
    Dummy Top Plate .STL File for 3D printing
2016-10-25 Dummy Battery Pack
    Dummy Battery Pack .STL File for 3D Printing
2016-10-25 Dummy USB Port for Dummy Base Plate
    Dummy USB Port .STL File for 3D Printing. The Dummy USB Port is used to complete the Dummy Base Plate.
2018-08-22 Create LICENSE
2019-06-21 Add link to SCK 2.0
